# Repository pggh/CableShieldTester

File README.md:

# CableShieldTester

This is a simple build-it-yourself device that allows you to test
whether a cable is shielded or not. The device is easy and fast to use,
however, depending on the connector type you are dealing with, you need
a connector or adapter to get access to the signal lines.
There must be nothing connected to the other side of the cable.

The design is based on an ATtiny84 micro-controller so you will need a
programmer for it to build your device. (Any of the ATtiny24, ATtiny24A,
ATtiny44, ATtiny44A, ATtiny84, ATtiny84A will work.)

This video shows the test of an unshielded cable (**play with sound!**):

https://github.com/user-attachments/assets/809c1926-0d2f-4c97-92ae-36a32c1142be

More tests can be found [here](doc).

Build instructions are in the [hardware directory](hardware).

Discus at the [EEVblog Forum](https://www.eevblog.com/forum/projects/cableshieldtester-is-the-cable-shielded-or-not-(diy-project)/msg6097537/)

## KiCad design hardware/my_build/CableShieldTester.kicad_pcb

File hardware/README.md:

# Hardware build instructions

There are two sets of schematics and PCBs:

- [template](template) contains the files you can use as a start
  to build your own device. The schematics and layout does not contain
  the power section, so you can choose what is suitable for your
  needs.  
  \
  
- [my_build](my_build) contains the full schematics and layout of what I actually
  built for myself as a reference.  
  \
  \
  \
  \
  \

# Layout and cables

- Keep output components and connection close to the Pin 6 and away form
  sense input.
- Use a shielded cable for the output signal. The shield (connected to
  GND) should go as close to the output components and the external
  output clip as possible. The GND clip can be connected to either side
  of the shield of the output cable.
- Keep sense input components and connection close to the input pins.
- Use a unshielded cable for the sense input to keep the input capacity
  low.

# Powering

The power source is critical. Due to the measurement principle of the
device, VCC must be rather stable within a measurement cycle of 20ms.

The ideal power source is a battery. A 3.6V lithium battery (non
rechargeable or rechargeable) or 3 AAA cells (alkaline or NiMH)

When using external power, the source should not have much ripple and a
proper voltage regulation. Many cheap USB chargers fail in both
disciplines. Also the power source must not have any mains common-mode
signal. Use either a power-bank or a mains power supply that has an
earth referenced output.

The usual 2 pin (mains) chargers have a Y2 capacitor from the mains to
the GND of the output and therefore a common-mode 50/60Hz signal of up
to 300Vpp. This is not acceptable for the high impedance measurement of
the cable tester and might even damage it.

When using power-banks, practically all modern ones require a minimal
load to stay on. I tested my build (consumes 43 mA with the two LEDs)
with 4 different power-banks a the current was sufficient for two of them
to stay on but not for the other two.

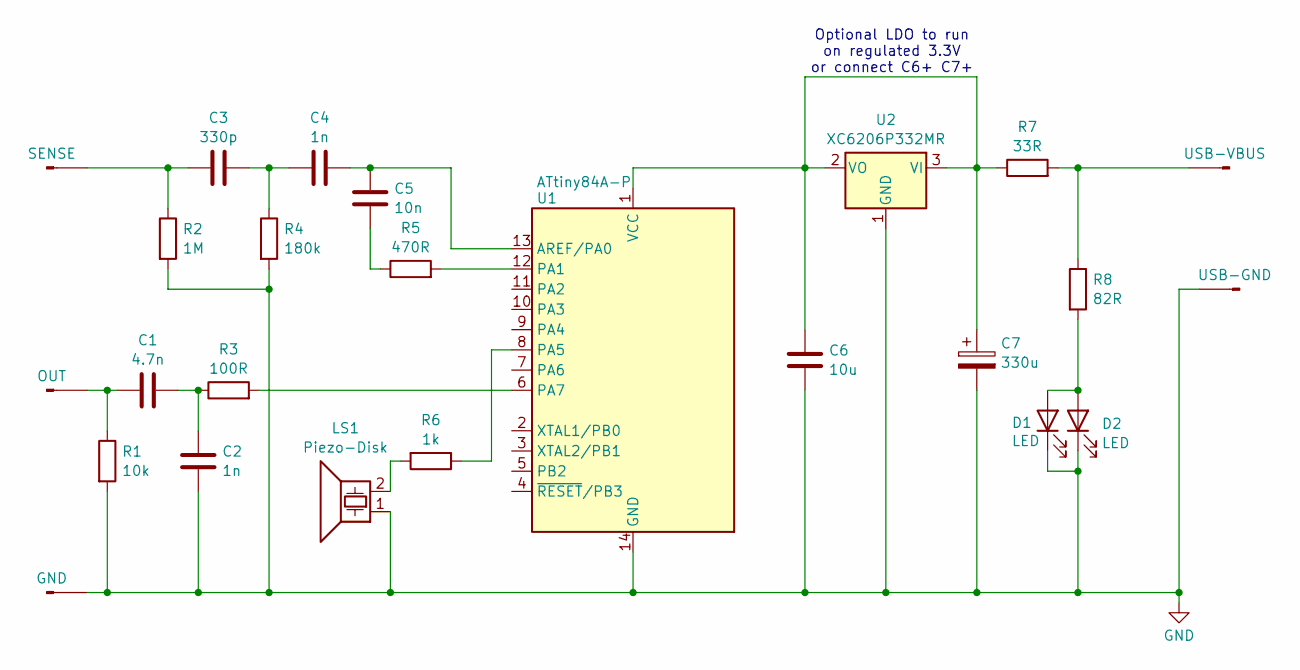
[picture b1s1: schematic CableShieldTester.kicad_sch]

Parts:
C1: 4.7n; C_0603_1608Metric
C2, C4: 1n; C_0603_1608Metric
C3: 330p; C_0603_1608Metric
C5: 10n; C_0603_1608Metric
C6: 10u; C_0603_1608Metric
C7: 330u; C_Radial_D6.3mm_H11.0mm_P2.50mm
D1, D2: LED; LED_0603_1608Metric
J1: SENSE; Pad_84mil
J2: OUT; Pad_84mil
J3: GND; Pad_84mil
J4: USB-VBUS; Pad_84mil
J5: USB-GND; Pad_84mil
LS1: Piezo-Disk; PinHeader_1x02_P2.54mm_Vertical
R1: 10k; R_0603_1608Metric
R2: 1M; R_0603_1608Metric
R3: 100R; R_0603_1608Metric
R4: 180k; R_0603_1608Metric
R5: 470R; R_0603_1608Metric
R6: 1k; R_0603_1608Metric
R7: 33R; R_0603_1608Metric
R8: 82R; R_0603_1608Metric
U1: ATtiny84A-P; DIP-14_W7.62mm
U2: XC6206P332MR; SOT-23-3

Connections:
GND: C2.2, C6.2, C7.2, D1.1 (K), D2.1 (K), J3.1, J5.1, LS1.1, R1.2, R2.2, R4.2, U1.14 (GND), U2.1 (GND)
unnamed: C1.2, C2.1, R3.1
unnamed: C3.2, C4.1, R4.1
unnamed: C5.2, R5.1
unnamed: D1.2 (A), D2.2 (A), R8.2
unnamed: C3.1, J1.1, R2.1
unnamed: C1.1, J2.1, R1.1
unnamed: J4.1, R7.2, R8.1
unnamed: LS1.2, R6.2
unnamed: C4.2, C5.1, U1.13 (AREF/PA0)
unnamed: R5.2, U1.12 (PA1)
unnamed: R6.1, U1.8 (PA5)
unnamed: R3.2, U1.6 (PA7)
unnamed: C6.1, C7.1, R7.1, U1.1 (VCC), U2.2 (VO), U2.3 (VI)

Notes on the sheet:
Optional LDO to run on regulated 3.3V or connect C6+ C7+

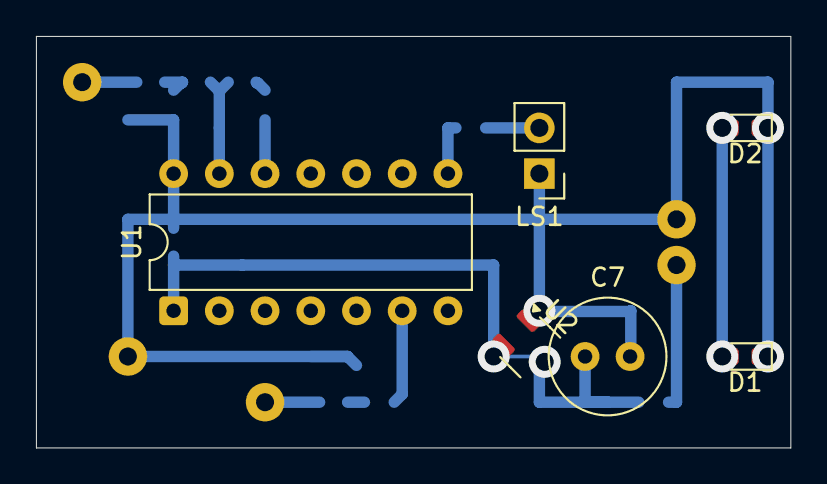
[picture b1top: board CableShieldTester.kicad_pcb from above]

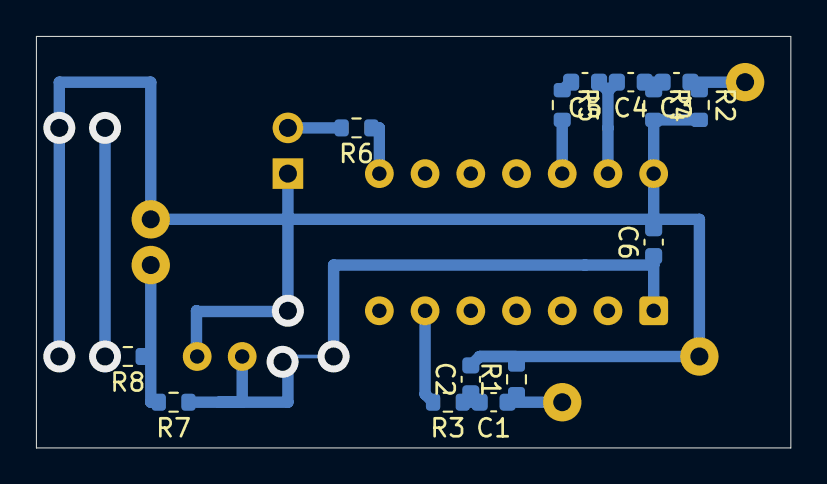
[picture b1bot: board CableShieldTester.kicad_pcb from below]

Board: 2 copper layers, 41.9 x 22.9 mm, 25 parts (14 on the bottom side), 14 nets.

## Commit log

2025-11-10 initial import
2025-11-10 Add link to EEVblog Forum
